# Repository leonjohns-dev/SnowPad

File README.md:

# SnowPad

**SnowPad is a 3x4 macro pad made for the Stardance Hack Club challenge**

### Features

- 12 Switches
- RGB Backlight
- OLED Screen
- RGB Lamp
- Water Drink Reminder *Upcoming Feature*

## Shematic

## PCB

- The PCB was designed using KiCad
- The 3d model was made using assets from Scotto Keeb's library of items
- Footprints come from KiCad and the Stardance care package

| Normal PCB View | Kicad 3D view |
| --------------- | ------------- |
|  |  |

### BOM

| Part | Quantity |
| --------------- | ------------- |
| Mx Switches | 12 |
| Keycaps | 12 |
| 1N4148 Diodes | 12 | 
| SK6812MINI-E RGB LEDs | 18 |
| Seeed Studio XIAO RP2040 | 1 |
| 0.91 inch OLED display | 1 |

## CAD

- For the CAD, I am using Fusion 360 with the imported KiCad models
- The CAD consists of a bottom case and a top plate, which are both joined through 4 m3 screws and 4 heat inserts.

| Altogether | Bottom | Top Plate |
| --------------- | ------------- | ------------- | 
|  |  | 

### Case parts

| Part | Quantity |
| --------------- | ------------- |
| Top Plate | 1 |
| Bottom Container | 1 |
| M3x16mm screws | 4 | 
| M3x5mx4mm heatset inserts | 4 |

## Firmware

- Firmware took me a while to figure out😭
- I first tried QMK, but it had no 4x3 layouts; I tried making my own layout, which failed
- The current firmware is built on kmk which is pretty straightforward.
- Firmware was made with assistance from ChatGPT.

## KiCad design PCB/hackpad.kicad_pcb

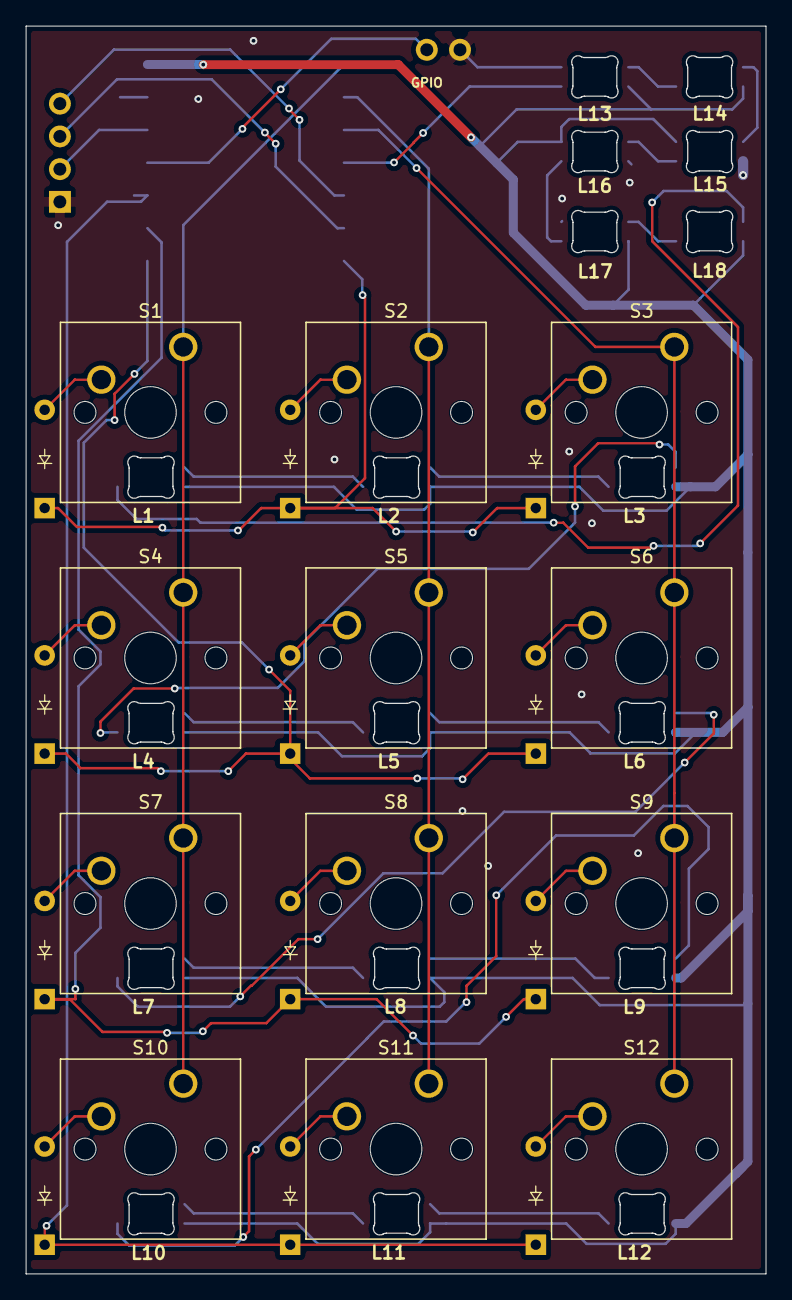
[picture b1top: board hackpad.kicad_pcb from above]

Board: 2 copper layers, 57.4 x 96.8 mm, 46 parts (1 on the bottom side), 43 nets.

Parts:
D1, D2, D3, D4, D5, D6, D7, D8, D9, D10, D11, D12: Diode_DO-35
J1: OLED_128x32
L1, L2, L3, L4, L5, L6, L7, L8, L9, L10, L11, L12, L13, L14, L15, L16, L17, L18: SK6812MINI-E; SK6812MINI-E_fixed
S1, S2, S3, S4, S5, S6, S7, S8, S9, S10, S11, S12: SW_Cherry_MX_1.00u_PCB
TP1, TP2: TestPoint
U1: MOUDLE-SEEEDUINO-XIAO; XIAO-Generic-Hybrid-14P-2.54-21X17.8MM_1

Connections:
+3V3: J1.2 (VCC), U1.12 (3V3)
+5V: L1.1 (VDD), L2.1 (VDD), L3.1 (VDD), L4.1 (VDD), L5.1 (VDD), L6.1 (VDD), L7.1 (VDD), L8.1 (VDD), L9.1 (VDD), L10.1 (VDD), L11.1 (VDD), L12.1 (VDD), L13.1 (VDD), L14.1 (VDD), L15.1 (VDD), L16.1 (VDD), L17.1 (VDD), L18.1 (VDD), U1.14 (5V)
Coloumn 1: S1.1, S4.1, S7.1, S10.1, U1.1 (PA02_A0_D0)
Coloumn 2: S2.1, S5.1, S8.1, S11.1, U1.2 (PA4_A1_D1)
Coloumn 3: S3.1, S6.1, S9.1, S12.1, U1.3 (PA10_A2_D2)
DIN: L13.4 (DIN), U1.4 (PA11_A3_D3)
GND: J1.1 (GND), L1.3 (VSS), L2.3 (VSS), L3.3 (VSS), L4.3 (VSS), L5.3 (VSS), L6.3 (VSS), L7.3 (VSS), L8.3 (VSS), L9.3 (VSS), L10.3 (VSS), L11.3 (VSS), L12.3 (VSS), L13.3 (VSS), L14.3 (VSS), L15.3 (VSS), L16.3 (VSS), L17.3 (VSS), L18.3 (VSS), TP2.1 (1_1), U1.13 (GND)
unnamed: D1.2 (A), S1.2
unnamed: D2.2 (A), S2.2
unnamed: D3.2 (A), S3.2
unnamed: D4.2 (A), S4.2
unnamed: D5.2 (A), S5.2
unnamed: D6.2 (A), S6.2
unnamed: D7.2 (A), S7.2
unnamed: D8.2 (A), S8.2
unnamed: D9.2 (A), S9.2
unnamed: D10.2 (A), S10.2
unnamed: D11.2 (A), S11.2
unnamed: D12.2 (A), S12.2
unnamed: L1.4 (DIN), L18.2 (DOUT)
unnamed: L1.2 (DOUT), L2.4 (DIN)
unnamed: L2.2 (DOUT), L3.4 (DIN)
unnamed: L3.2 (DOUT), L4.4 (DIN)
unnamed: L4.2 (DOUT), L5.4 (DIN)
unnamed: L5.2 (DOUT), L6.4 (DIN)
unnamed: L6.2 (DOUT), L7.4 (DIN)
unnamed: L7.2 (DOUT), L8.4 (DIN)
unnamed: L8.2 (DOUT), L9.4 (DIN)
unnamed: L9.2 (DOUT), L10.4 (DIN)
unnamed: L10.2 (DOUT), L11.4 (DIN)
unnamed: L11.2 (DOUT), L12.4 (DIN)
unnamed: L13.2 (DOUT), L14.4 (DIN)
unnamed: L14.2 (DOUT), L15.4 (DIN)
unnamed: L15.2 (DOUT), L16.4 (DIN)
unnamed: L16.2 (DOUT), L17.4 (DIN)
unnamed: L17.2 (DOUT), L18.4 (DIN)
unnamed: TP1.1 (1_1), U1.11 (PA6_A10_D10_MOSI)
OLED_SCL: J1.3 (SCL), U1.6 (PA9_A5_D5_SCL)
OLED_SDA: J1.4 (SDA), U1.5 (PA8_A4_D4_SDA)
Row 1: D1.1 (K), D2.1 (K), D3.1 (K), U1.7 (PB08_A6_D6_TX)
Row 2: D4.1 (K), D5.1 (K), D6.1 (K), U1.8 (PB09_A7_D7_RX)
Row 3: D7.1 (K), D8.1 (K), D9.1 (K), U1.9 (PA7_A8_D8_SCK)
Row 4: D10.1 (K), D11.1 (K), D12.1 (K), U1.10 (PA5_A9_D9_MISO)
